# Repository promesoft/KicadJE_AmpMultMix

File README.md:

# Johansen Engineering KicadJE_AmpMultMix
KicadJE_AmpMultMix - INCOMPLETE

# Purpose
NOTE - INITIALLY THE PROJECT "KiCadJE_LFO_1" will do the validation of the initial design of the MMX
# Status - Preliminary SCH/PCB
## Initial 
| Stage  | Detail | Status |
| ------------- | ------------- | ------------- |
| create material  | sch/pcb |   |
| | gerber | |
| production  |   |  |
|  | produced |  |
|  | delivered |  |
## Preliminary validation
| Test  | Detail | Status |
| ------------- | ------------- | ------------- |
| Initial Inspection | |  |
| Initial Technical Test |  |  |
| Initial Product Test | VCO CV from LFO | OK |

## Secondary validation
| Test  | Detail | Status |
| ------------- | ------------- |------------- |
| Product Test |  | |
| Product Test |  |  |
| Quality | | |
| Quality | | |
| Long Term Product Test |  |  |
| Power Draw |  | 

## Errata
### Errata -

## Issues and Notes
###

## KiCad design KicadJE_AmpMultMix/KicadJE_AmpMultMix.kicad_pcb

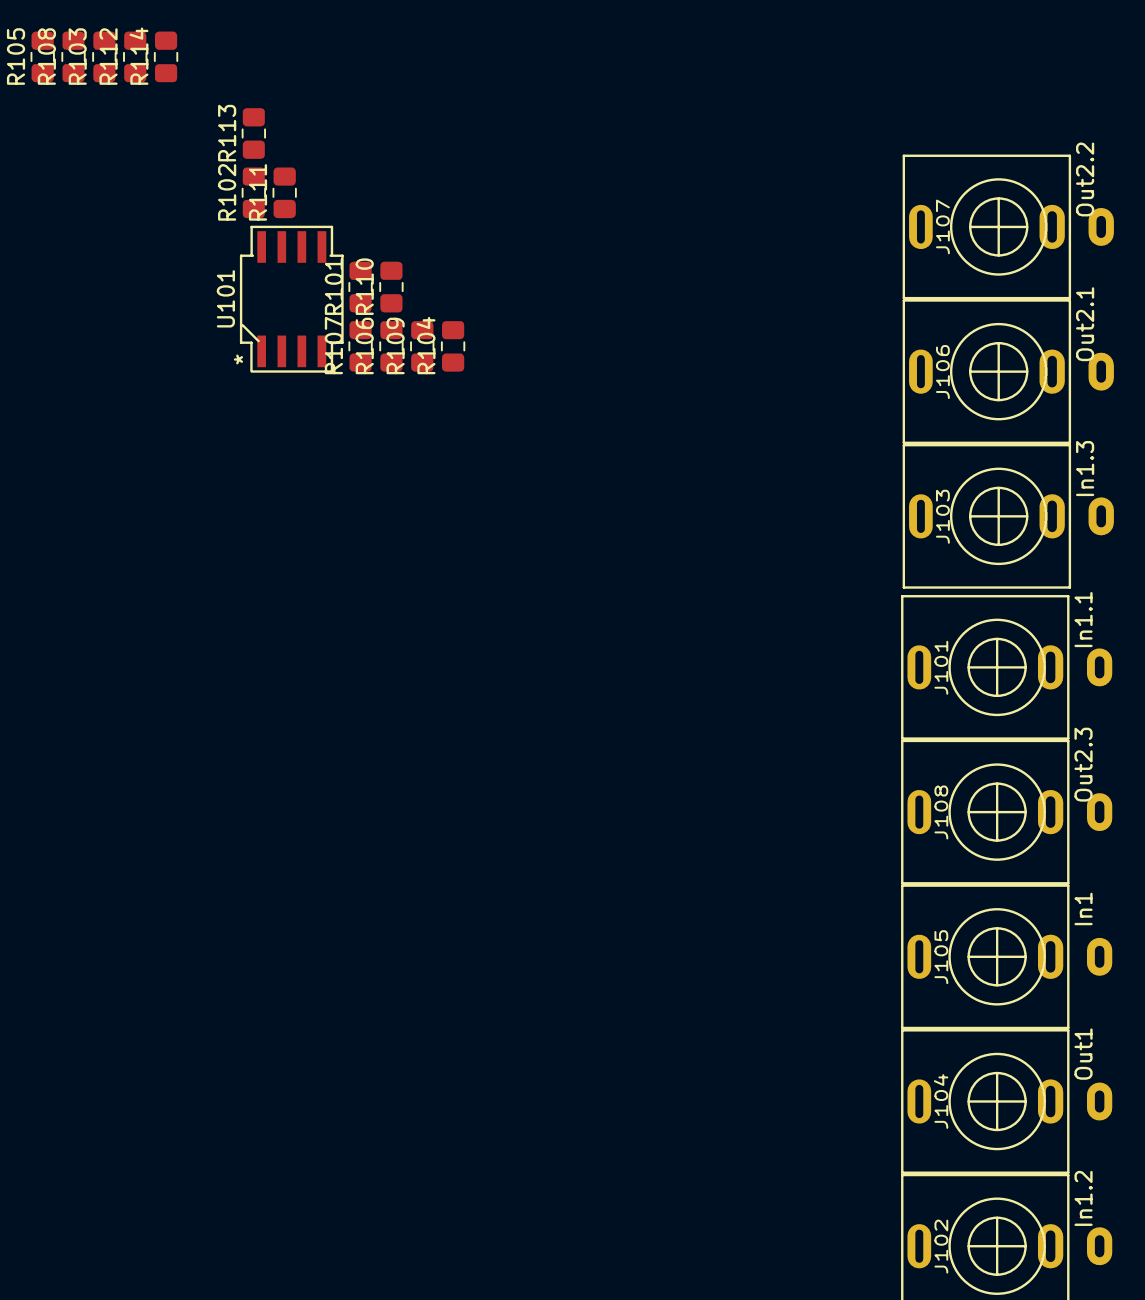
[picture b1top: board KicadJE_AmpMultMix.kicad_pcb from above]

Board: 2 copper layers, 23 parts (0 on the bottom side), 16 nets, no tracks yet.

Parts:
J101: In1.1; PJ301SM
J102: In1.2; PJ301SM
J103: In1.3; PJ301SM
J104: Out1; PJ301SM
J105: In1; PJ301SM
J106: Out2.1; PJ301SM
J107: Out2.2; PJ301SM
J108: Out2.3; PJ301SM
R101, R103, R104, R105, R106, R108, R110, R112: 47k; R_0805_2012Metric_Pad1.15x1.40mm_HandSolder
R102, R109: 20k; R_0805_2012Metric_Pad1.15x1.40mm_HandSolder
R107, R111, R113, R114: 4k7; R_0805_2012Metric_Pad1.15x1.40mm_HandSolder
U101: TL082; AJ_SO-8_5.3x6.2mm_P1.27mm

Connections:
GND: J101.S, J101.TN, J102.S, J102.TN, J103.S, J103.TN, J104.S, J105.S, J106.S, J106.TN, J107.S, J107.TN, R101.2, R106.1, R108.2, R112.1
In1: R103.1, R104.1, R105.1
unnamed: J101.T, R103.2
unnamed: J102.T, R104.2
unnamed: J103.T, R105.2
unnamed: J104.T, J105.TN, R107.2
unnamed: J105.T, R110.2
unnamed: J106.T, R111.2
unnamed: J107.T, R113.2
unnamed: J108.T, R114.2
unnamed: R101.1, R102.2, U101.2
unnamed: R106.2, U101.3
unnamed: R108.1, R109.2, U101.6
unnamed: R112.2, U101.5
Out1: R102.1, R107.1, U101.1
Out2: R109.1, R111.1, R113.1, R114.1, U101.7

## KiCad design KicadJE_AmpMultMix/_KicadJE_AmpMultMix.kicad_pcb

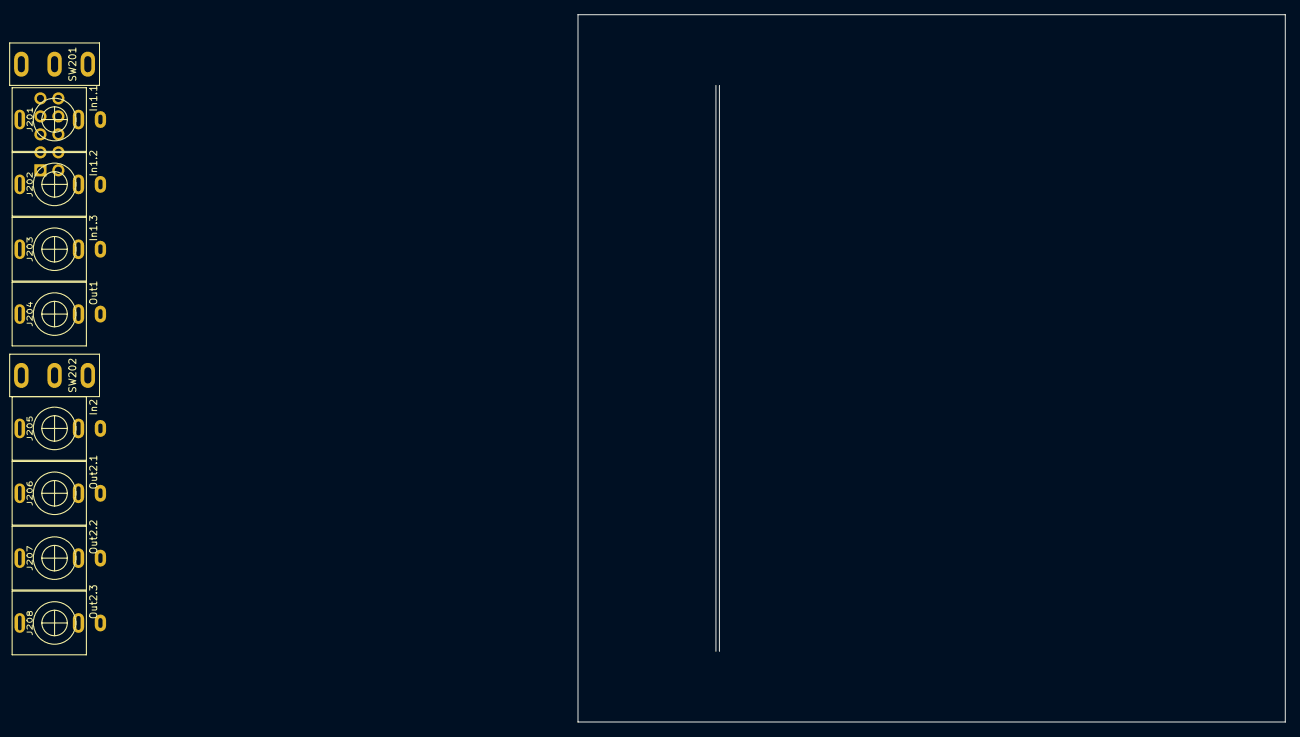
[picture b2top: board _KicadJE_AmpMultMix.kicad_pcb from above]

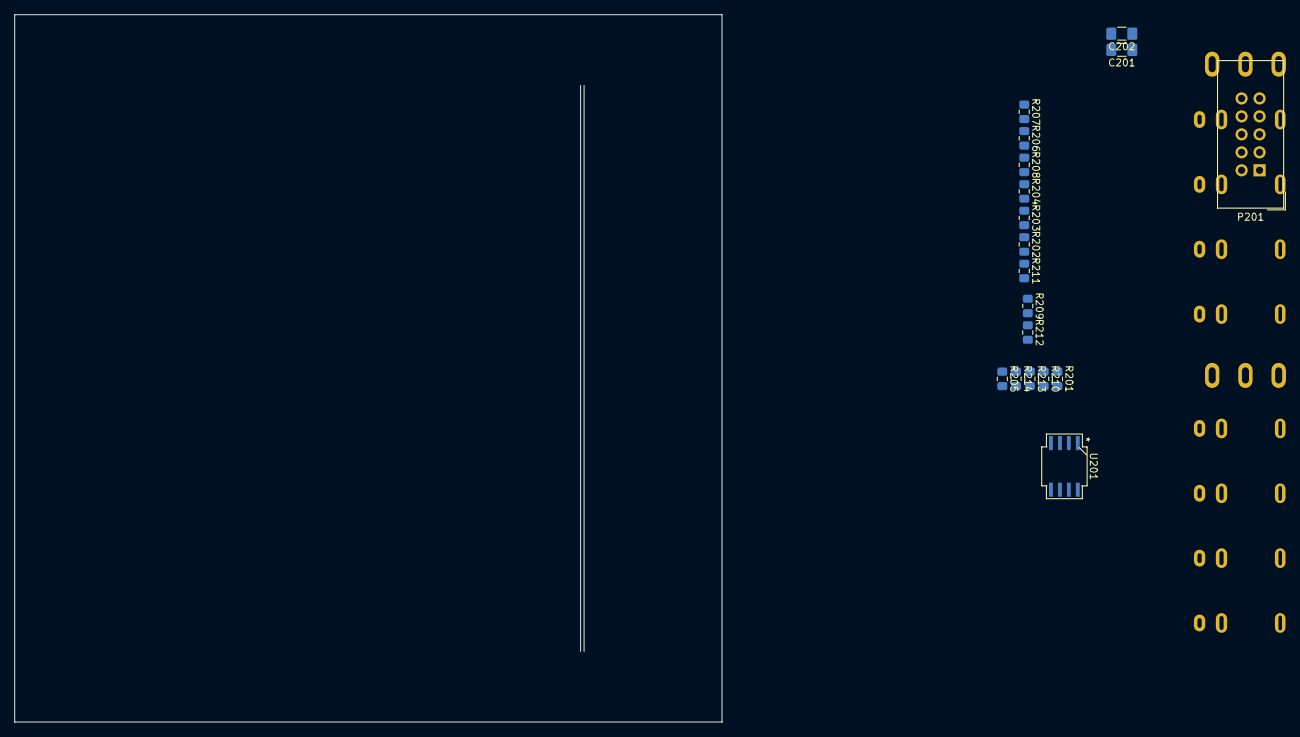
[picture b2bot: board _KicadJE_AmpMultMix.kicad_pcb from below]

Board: 2 copper layers, 100.0 x 100.0 mm, 28 parts (18 on the bottom side), 21 nets, no tracks yet.

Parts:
C201, C202: 1u; C_1206_3216Metric_Pad1.42x1.75mm_HandSolder
J201: In1.1; PJ301SM
J202: In1.2; PJ301SM
J203: In1.3; PJ301SM
J204: Out1; PJ301SM
J205: In2; PJ301SM
J206: Out2.1; PJ301SM
J207: Out2.2; PJ301SM
J208: Out2.3; PJ301SM
P201: HEADER_2x5_Doepfer; IDC-Header_2x05_P2.54mm_Vertical
R201, R203, R204, R205, R206, R208, R210, R212: 47k; R_0805_2012Metric_Pad1.15x1.40mm_HandSolder
R202, R209: 20k; R_0805_2012Metric_Pad1.15x1.40mm_HandSolder
R207, R211, R213, R214: 4k7; R_0805_2012Metric_Pad1.15x1.40mm_HandSolder
SW201, SW202: Inv/NonInv; SP1MS1
U201: TL082; AJ_SO-8_5.3x6.2mm_P1.27mm

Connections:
GND: J201.S, J201.TN, J202.S, J202.TN, J203.S, J203.TN, J204.S, J205.S, J206.S, J207.S, J208.S, R201.2, R206.1, R208.2, R212.1
In1: R203.1, R204.1, R205.1, SW201.2
In2: R210.1, SW202.2
unnamed: C201.1, P201.9, P201.10, U201.8
unnamed: C201.2, C202.1, P201.3, P201.5, P201.7
unnamed: C202.2, P201.1, P201.2, U201.4
unnamed: J201.T, R203.2
unnamed: J202.T, R204.2
unnamed: J203.T, R205.2
unnamed: J204.T, J205.TN, R207.2
unnamed: J205.T, R210.2
unnamed: J206.T, R211.2
unnamed: J207.T, R213.2
unnamed: J208.T, R214.2
unnamed: P201.4, P201.6, P201.8
unnamed: R201.1, R202.2, SW201.1, U201.2
unnamed: R206.2, SW201.3, U201.3
unnamed: R208.1, R209.2, SW202.1, U201.6
unnamed: R212.2, SW202.3, U201.5
Out1: R202.1, R207.1, U201.1
Out2: R209.1, R211.1, R213.1, R214.1, U201.7

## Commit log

2019-03-11 Init
2019-03-13 Initial PCB
2019-03-13 Switch for Inv/NonInv
2019-03-13 MultMix Subsheet + Power conn
2019-03-13 JE MMX1 - Front components placed
2019-03-15 555 LFO
2019-10-02 Create fp-info-cache
